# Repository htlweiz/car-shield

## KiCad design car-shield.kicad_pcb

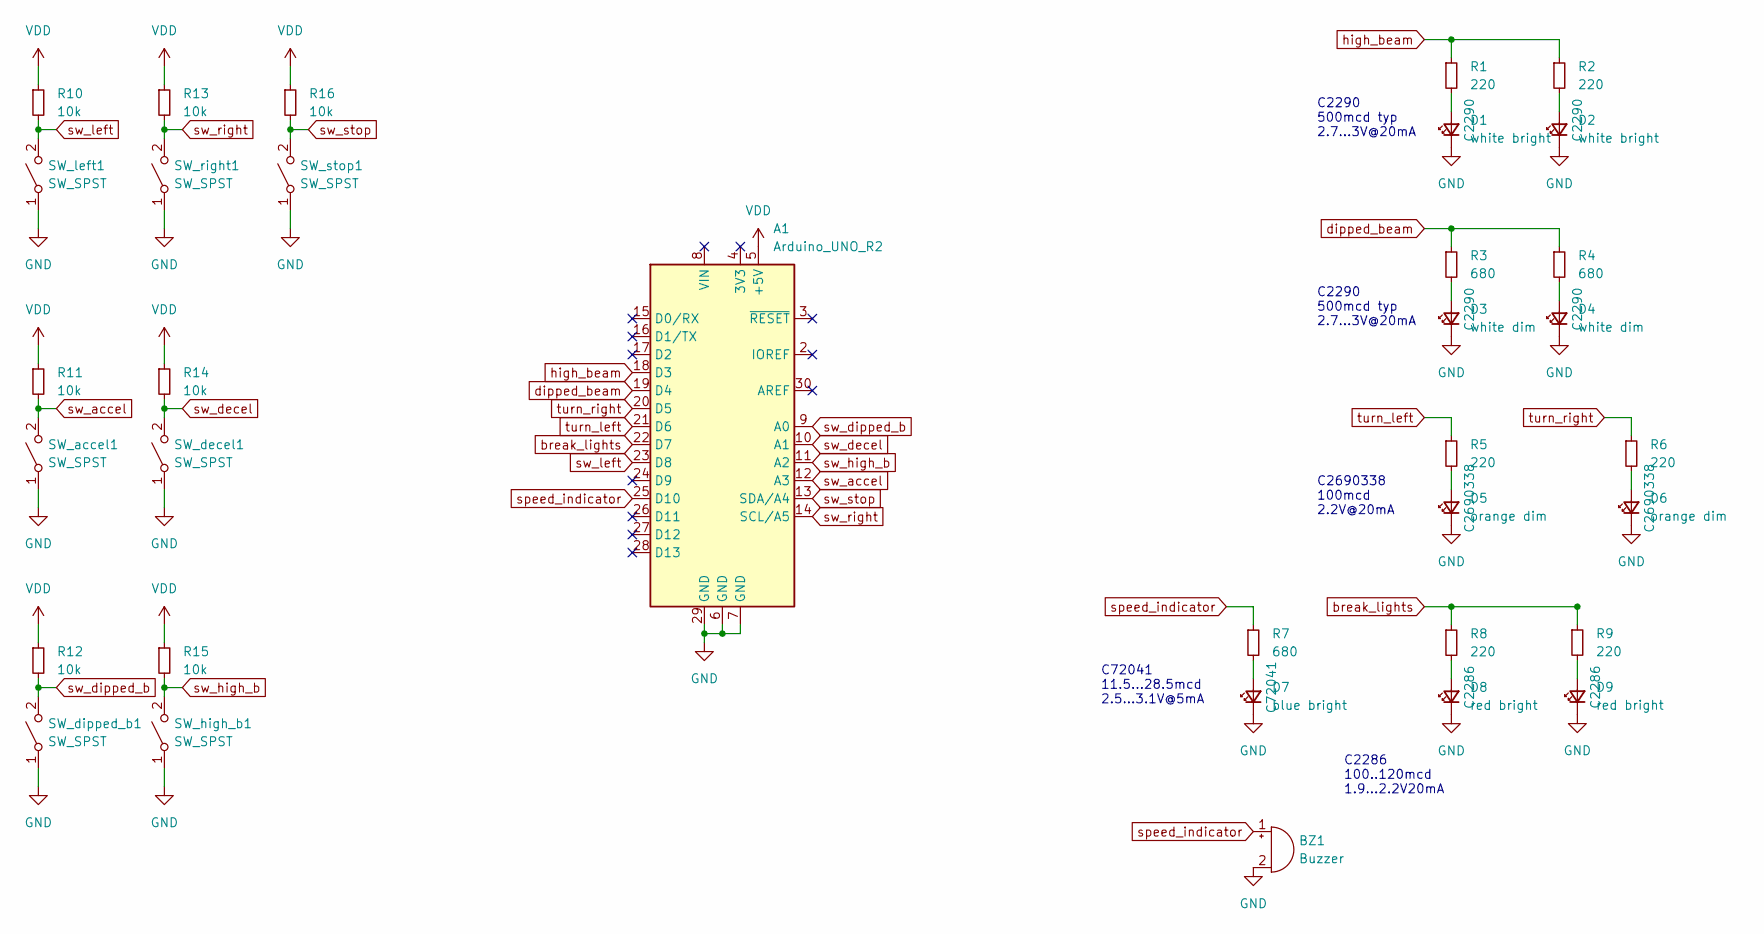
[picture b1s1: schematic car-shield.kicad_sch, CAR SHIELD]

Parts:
A1: Arduino_UNO_R2
BZ1: Buzzer; Buzzer_15x7.5RM7.6
D1, D2: white bright; LED_0603_1608Metric; LCSC C2290
D3, D4: white dim; LED_0603_1608Metric; LCSC C2290
D5, D6: orange dim; LED_0603_1608Metric; LCSC C2690338
D7: blue bright; LED_0603_1608Metric; LCSC C72041
D8, D9: red bright; LED_0603_1608Metric; LCSC C2286
R1, R2, R5, R6, R8, R9: 220; R_0402_1005Metric; LCSC C25091
R3, R4, R7: 680; R_0402_1005Metric; LCSC C25130
R10, R11, R12, R13, R14, R15, R16: 10k; R_0402_1005Metric; LCSC C25744
SW_accel1: SW_SPST; SW_SPST_SKQG_WithoutStem; LCSC C318884
SW_decel1: SW_SPST; SW_SPST_SKQG_WithoutStem; LCSC C318884
SW_dipped_b1: SW_SPST; SW_SPST_SKQG_WithoutStem; LCSC C318884
SW_high_b1: SW_SPST; SW_SPST_SKQG_WithoutStem; LCSC C318884
SW_left1: SW_SPST; SW_SPST_SKQG_WithoutStem; LCSC C318884
SW_right1: SW_SPST; SW_SPST_SKQG_WithoutStem; LCSC C318884
SW_stop1: SW_SPST; SW_SPST_SKQG_WithoutStem; LCSC C318884

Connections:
GND: A1.6 (GND), A1.7 (GND), A1.29 (GND), BZ1.2 (+), D1.1 (K), D2.1 (K), D3.1 (K), D4.1 (K), D5.1 (K), D6.1 (K), D7.1 (K), D8.1 (K), D9.1 (K), SW_accel1.1 (A), SW_decel1.1 (A), SW_dipped_b1.1 (A), SW_high_b1.1 (A), SW_left1.1 (A), SW_right1.1 (A), SW_stop1.1 (A)
unnamed: D1.2 (A), R1.2
unnamed: D2.2 (A), R2.2
unnamed: D3.2 (A), R3.2
unnamed: D4.2 (A), R4.2
unnamed: D5.2 (A), R5.2
unnamed: D6.2 (A), R6.2
unnamed: D7.2 (A), R7.2
unnamed: D8.2 (A), R8.2
unnamed: D9.2 (A), R9.2
VDD: A1.5 (+5V), R10.1, R11.1, R12.1, R13.1, R14.1, R15.1, R16.1
break_lights: A1.22 (D7), R8.1, R9.1
dipped_beam: A1.19 (D4), R3.1, R4.1
high_beam: A1.18 (D3), R1.1, R2.1
speed_indicator: A1.25 (D10), BZ1.1 (-), R7.1
sw_accel: A1.12 (A3), R11.2, SW_accel1.2 (B)
sw_decel: A1.10 (A1), R14.2, SW_decel1.2 (B)
sw_dipped_b: A1.9 (A0), R12.2, SW_dipped_b1.2 (B)
sw_high_b: A1.11 (A2), R15.2, SW_high_b1.2 (B)
sw_left: A1.23 (D8), R10.2, SW_left1.2 (B)
sw_right: A1.14 (SCL/A5), R13.2, SW_right1.2 (B)
sw_stop: A1.13 (SDA/A4), R16.2, SW_stop1.2 (B)
turn_left: A1.21 (D6), R5.1
turn_right: A1.20 (D5), R6.1

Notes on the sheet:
C2690338 100mcd 2.2V@20mA
C2286 100..120mcd 1.9...2.2V20mA
C2290 500mcd typ 2.7...3V@20mA
C72041 11.5...28.5mcd 2.5...3.1V@5mA

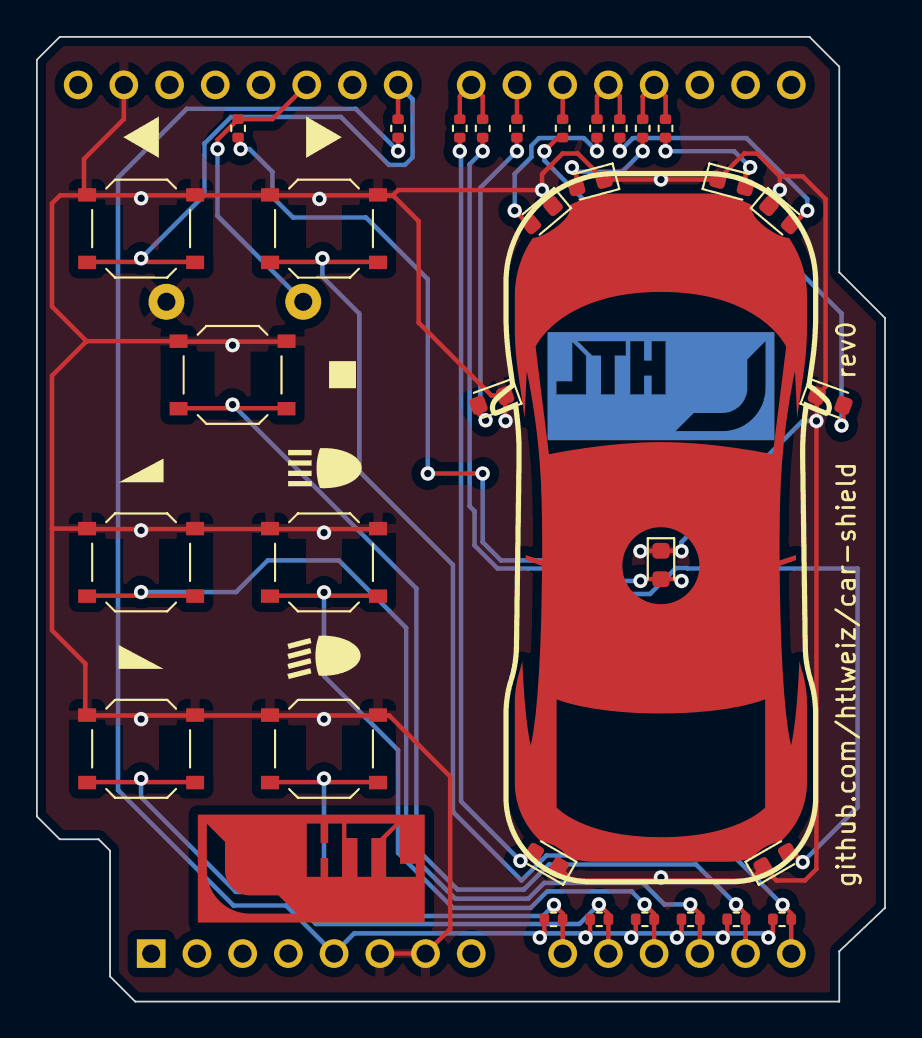
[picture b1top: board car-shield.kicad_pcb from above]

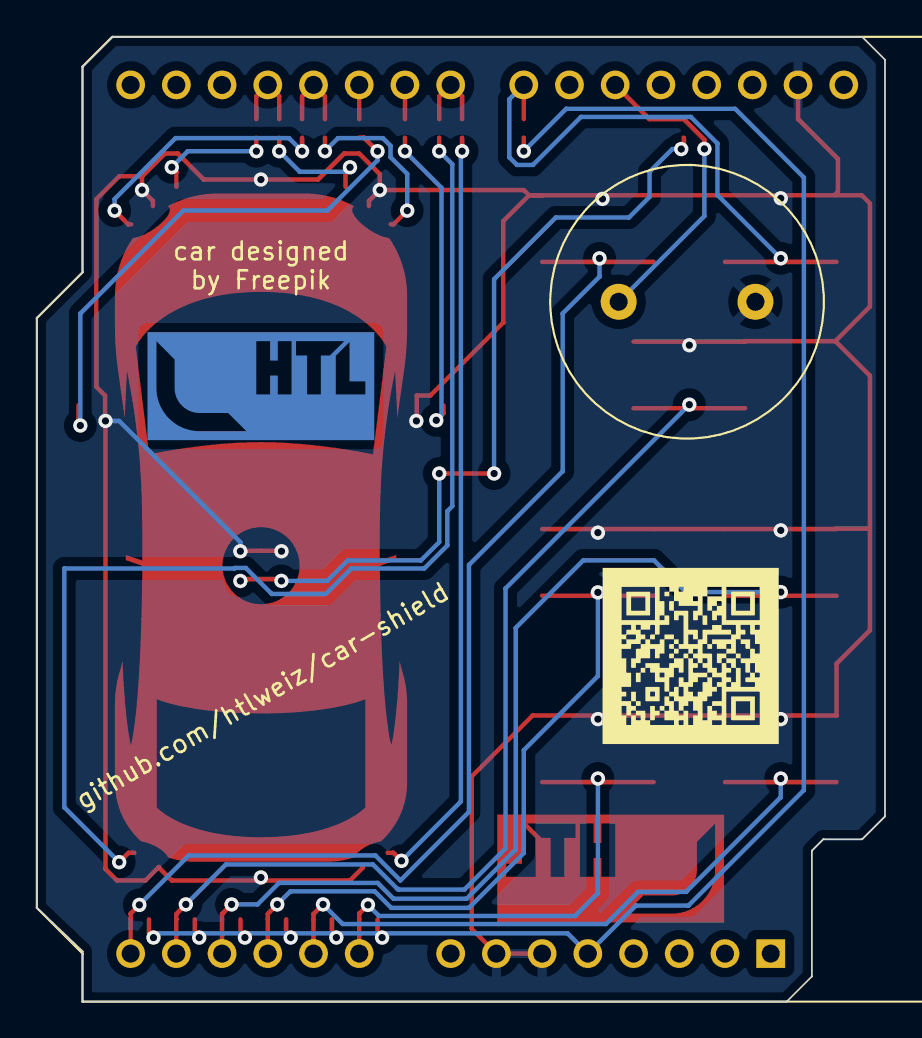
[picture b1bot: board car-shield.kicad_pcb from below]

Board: 2 copper layers, 47.1 x 53.6 mm, 34 parts (2 on the bottom side), 24 nets.

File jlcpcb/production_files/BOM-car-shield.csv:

Comment,Designator,Footprint,LCSC
red bright,"D8,D9",LED_0603_1608Metric,C2286
white bright,"D1,D2,D3,D4",LED_0603_1608Metric,C2290
220,"R1,R2,R5,R6,R8,R9",R_0402_1005Metric,C25091
680,"R3,R4,R7",R_0402_1005Metric,C25130
10k,"R10,R11,R12,R13,R14,R15,R16",R_0402_1005Metric,C25744
orange dim,"D5,D6",LED_0603_1608Metric,C2690338
SW_SPST,"SW_accel1,SW_decel1,SW_dipped_b1,SW_high_b1,SW_left1,SW_right1,SW_stop1",SW_SPST_TS-1187A,C318884
blue bright,D7,LED_0603_1608Metric,C72041
Buzzer,BZ1,Buzzer_15x7.5RM7.6,

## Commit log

2022-11-22 updated resistor parts and Freepik notice
2022-11-22 updated car footprint
2022-11-22 some initial routing
2022-11-30 added switch datasheet
2022-11-30 htl logo outline shrink
2022-11-30 layout tweaks
2022-11-30 added qrcode pointing to github repo
2022-11-30 final touches for revA
2022-11-30 rev0
